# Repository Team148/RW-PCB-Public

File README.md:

# RW-PCB-Public

Disclaimer: These were only designed, and prototyped but have not been tested.

These PCBs are RW version of the Talon SRX Breakout Board and a simple CAN Bus Daisy Chain Board. This is standardized around
the Molex SL latching type of connector (50-57-9405). This type of connector also connects to US Digital S5 Encoders
```
Talon SRX Breakout Board BOM
  Harwin M50-3000745     Qty 1 (Cut off outer 4 pins)
  Molex 15-91-3053       Qty 1
  Lite-On LTST-C171KRKT  Qty 1 (Optional)
  Susumu RR1220P-222-D   Qty 1 (Optional)
  
Based on MVRT / FRC Team 115's Open Source Design.
```

CAN Devices need to be wired into a Molex SL type connectors(50-579404) with the H (green) paired in the middle 2 positions,
and the L's on the outer two positions. The twisted pairs need to be next to each other. Devices must be plugged
in Sequentially and the last device must be terminated with an 120 Ohm resistor (can be PDP). These boards can also
be daisy chained if above 14 devices, simply attach port 13 to another board's port 0.The port numbers are just for reference,
they do not have to correspond to CAN ID.
```
RW CAN
  Molex 70543-0108       Qty 14
```
GERBER Files are exported for SEEEDSTUDIO's FUSION Service @ $4.90 + ship.

Update (2018/01/13): Breakouts are good to go. SMD LED and Resistors are a bit on the small side.

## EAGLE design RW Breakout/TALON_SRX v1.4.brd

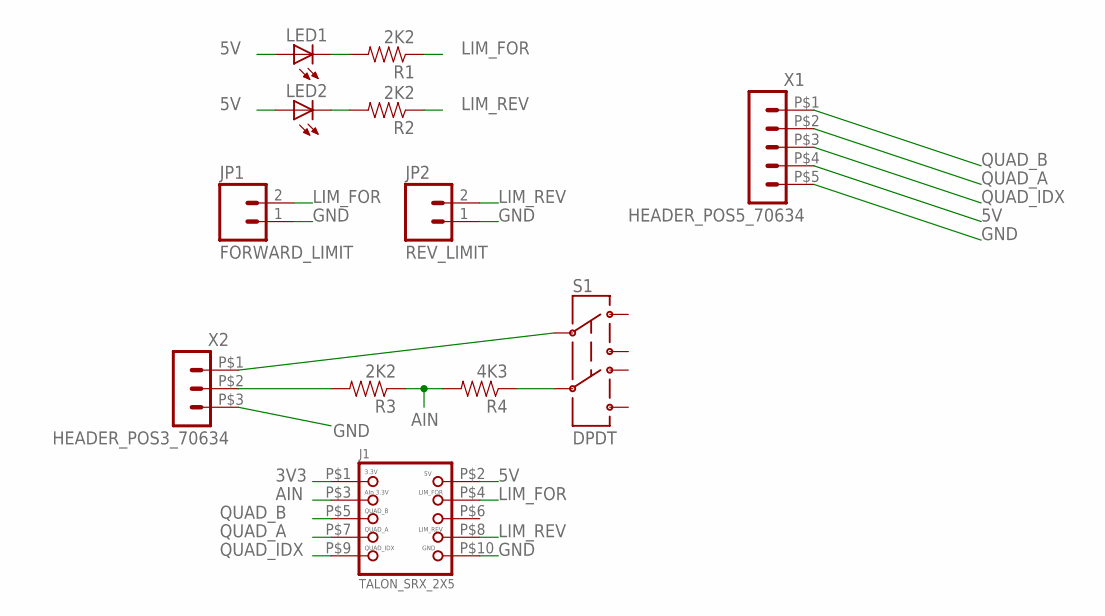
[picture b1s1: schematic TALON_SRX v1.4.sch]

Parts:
J1: TALON_SRX_2X5; 2X5-0.05-HEADER
JP1: FORWARD_LIMIT; MOLEX-1X2
JP2: REV_LIMIT; MOLEX-1X2
LED1, LED2: LEDCHIP-LED0805; CHIP-LED0805
R1, R2, R3: 2K2; 0805
R4: 4K3; 0805
S1: DPDT; AYZ0202
X1: HEADER_POS5_70634; 70634-POS5
X2: HEADER_POS3_70634; 70634-POS3

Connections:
3V3: J1.P$1 (1)
5V: J1.P$2 (2), LED1.A, LED2.A, X1.P$4 (4)
AIN: J1.P$3 (3), R3.1, R4.2
GND: J1.P$10 (10), JP1.1, JP2.1, X1.P$5 (5), X2.P$3 (3)
LIM_FOR: J1.P$4 (4), JP1.2, R1.1
LIM_REV: J1.P$8 (8), JP2.2, R2.1
unnamed: LED2.C, R2.2
unnamed: LED1.C, R1.2
unnamed: R3.2, X2.P$2 (2)
unnamed: R4.1, S1.5
unnamed: S1.2, X2.P$1 (1)
QUAD_A: J1.P$7 (7), X1.P$2 (2)
QUAD_B: J1.P$5 (5), X1.P$1 (1)
QUAD_IDX: J1.P$9 (9), X1.P$3 (3)

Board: 2 copper layers, 12 parts (1 on the bottom side), 13 nets, no tracks yet.

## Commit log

2018-01-05 Added Files
    Files are for an untested Talon SRX Breakout and a CAN Daisy Chain Board

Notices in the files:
parts and their libraries:
SparkFun-Connectors: Licensing: Creative Commons ShareAlike 4.0 International - https://creativecommons.org/licenses/by-sa/4.0
